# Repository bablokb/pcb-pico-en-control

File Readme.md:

Pico EN Control
===============

This is a simple breakout to control the enable pin of a Pico to
minimize battery usage.

Functions:
  * Enable using a button, a RTC or an external signal
  * Disable by pulling a GPIO high from your program
  * keep time

The target application of this design is a program that runs in
intervals. After startup the program executes it's tasks, sets
the next wakup time and then pulls the "done"-GPIO high.
The circuitry then pulls the enable-pin low, thus limiting the
battery consumption to a very low level.

The design of the breakout allows it to be connected directly on the bottom
side of the pico. Note that the breakout uses a solderless layout for the
pins, i.e. it will hold by friction. But don't expect miracles, it may
or may not work depending on your pins. For production use, you should
definitely solder the breakout.

Hardware Components
-------------------

A D-type flip-flop drives the enable pin of the Pico. A
button, the RTC or an external signal will reset the flip-flop,
which pulls the enable pin high.

The "done"-pin of the Pico is connected to the CLK-pin of
the flip-flop. A rising edge will toggle the enable pin.

PCB
---

PCB design files are in `pico-en-control.kicad`.

Ready to use production files for JLCPCB are in `production_files`.

Software
--------

A simple example program implemented in CircuitPython
is provided in `src/main.py`. The software provides some boilerplate
code for timer and alarm-based wake up.

In timer-mode, the program uses the countdown-timer of the rtc. It
blinks the on-board LED for ten seconds, then goes to sleep for 15 seconds.

Measured current:

For longer intervals alarm-based wake up is more suitable. Since the rtc
does not support seconds for alarms, it will always fire on "full minutes".
The current measurement demonstrates this behavior (the first off-interval
is shorter than the following off-intervals):

Current in off-state is about 75µA (with CLKOUT disabled):

License
-------

[![CC BY-SA 4.0][cc-by-sa-shield]][cc-by-sa]

This work is licensed under a
[Creative Commons Attribution-ShareAlike 4.0 International
License][cc-by-sa].

[![CC BY-SA 4.0][cc-by-sa-image]][cc-by-sa]

[cc-by-sa]: http://creativecommons.org/licenses/by-sa/4.0/
[cc-by-sa-image]: https://licensebuttons.net/l/by-sa/4.0/88x31.png
[cc-by-sa-shield]:
https://img.shields.io/badge/License-CC%20BY--SA%204.0-lightgrey.svg

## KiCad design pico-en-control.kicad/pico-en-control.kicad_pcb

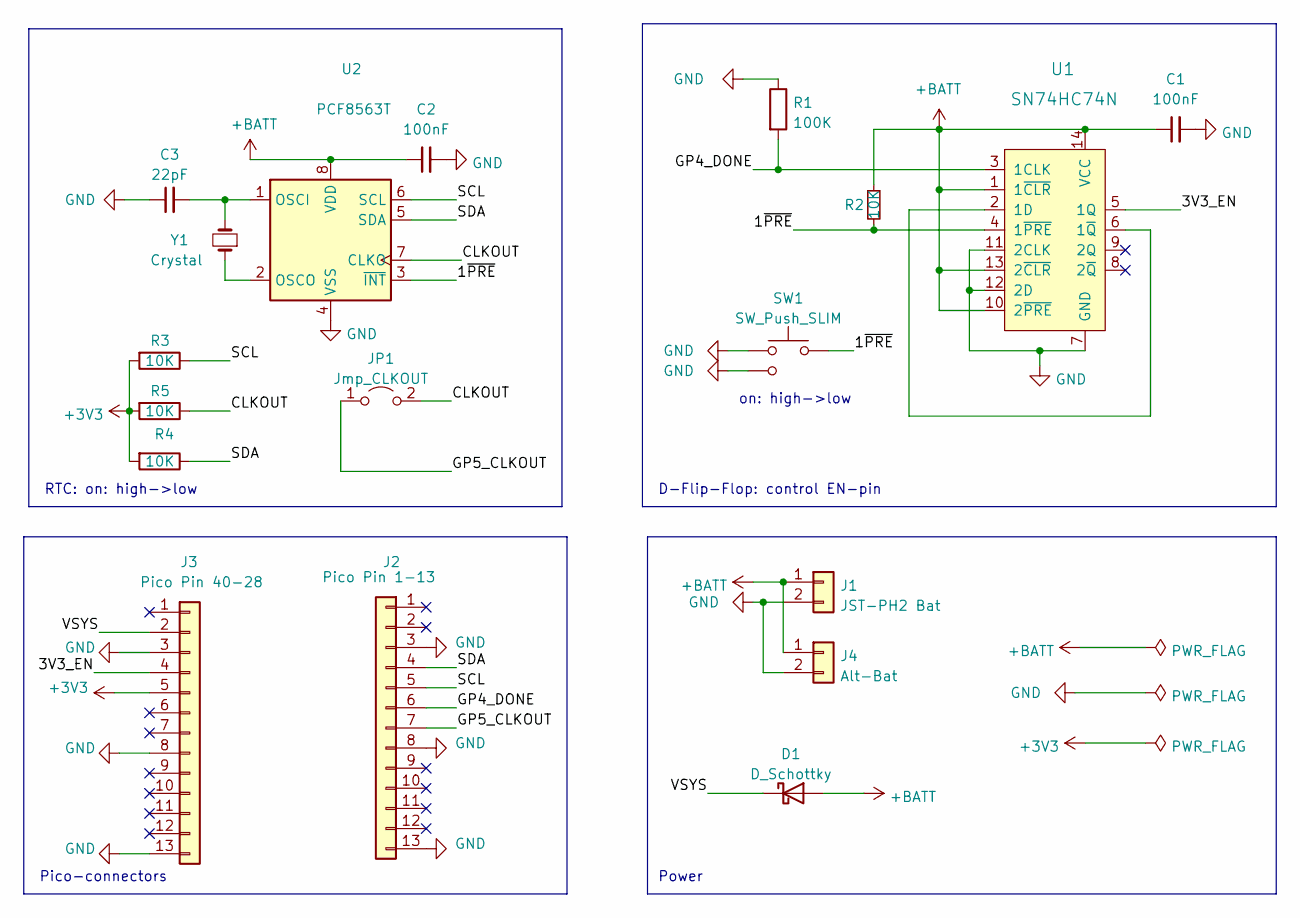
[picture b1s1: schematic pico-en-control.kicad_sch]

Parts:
C1, C2: 100nF; C_0402_1005Metric; LCSC C1525
C3: 22pF; C_0402_1005Metric; LCSC C1555
D1: D_Schottky; D_SMA; LCSC C2480
J1: JST-PH2 Bat; JST_PH_S2B-PH-SM4-TB_1x02-1MP_P2.00mm_Horizontal
J2: Pico Pin 1-13; Connector_1x13_no_solder
J3: Pico Pin 40-28; Connector_1x13_no_solder
J4: Alt-Bat; PinHeader_1x02_P2.54mm_Vertical
JP1: Jmp_CLKOUT; SolderJumper-2_P1.3mm_Open_Pad1.0x1.5mm
R1: 100K; R_0402_1005Metric; LCSC C25741
R2, R3, R4, R5: 10K; R_0402_1005Metric; LCSC C25744
SW1: SW_Push_SLIM; SW_PUSH_SLIM_1x4
U1: SN74HC74N; SOIC-14_3.9x8.7mm_P1.27mm; MPN SN74HC74N; Digi-Key_PN 296-1602-5-ND
U2: PCF8563T; SOIC-8_3.9x4.9mm_P1.27mm; LCSC C7440
Y1: Crystal; Crystal_SMD_3215-2Pin_3.2x1.5mm; LCSC C32346

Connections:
+3V3: J3.5, R3.2, R4.2, R5.2
+BATT: C1.1, C2.1, D1.2 (A), J1.1, J4.1, R2.1, U1.1 (1~CLR), U1.10 (2~PRE), U1.13 (2~CLR), U1.14 (VCC), U2.8 (VDD)
/1~PRE: R2.2, SW1.2, U1.4 (1~PRE), U2.3 (~INT)
/3V3_EN: J3.4, U1.5 (1Q)
/CLKOUT: JP1.2 (B), R5.1, U2.7 (CLKO)
/GP4_DONE: J2.6, R1.2, U1.3 (1CLK)
/GP5_CLKOUT: J2.7, JP1.1 (A)
/SCL: J2.5, R3.1, U2.6 (SCL)
/SDA: J2.4, R4.1, U2.5 (SDA)
/VSYS: D1.1 (K), J3.2
GND: C1.2, C2.2, C3.1, J1.2, J2.3, J2.8, J2.13, J3.3, J3.8, J3.13, J4.2, R1.1, SW1.1, SW1.3 (1), U1.7 (GND), U1.11 (2CLK), U1.12 (2D), U2.4 (VSS)
unnamed: C3.2, U2.1 (OSCI), Y1.2
unnamed: U1.2 (1D), U1.6 (1~Q)
unnamed: U2.2 (OSCO), Y1.1

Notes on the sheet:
Power
D-Flip-Flop: control EN-pin
Pico-connectors
RTC: on: high->low
on: high->low

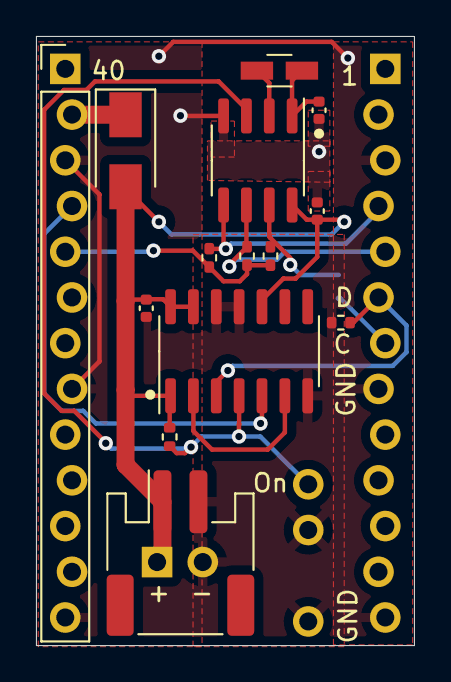
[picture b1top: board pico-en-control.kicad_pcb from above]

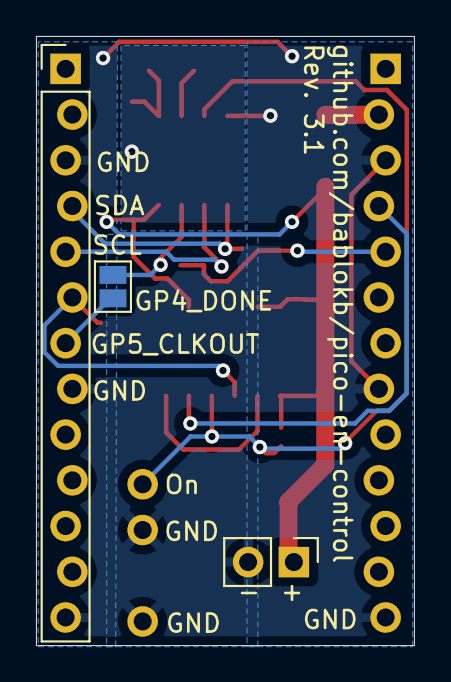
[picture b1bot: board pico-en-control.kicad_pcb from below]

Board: 2 copper layers, 21.0 x 33.8 mm, 18 parts (3 on the bottom side), 14 nets.

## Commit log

2023-01-25 fixed path of xml
2023-02-02 draft routing
2023-02-03 switched to 13-pin connectors
2023-02-03 DRC ok
2023-02-09 Rev2
2023-02-17 Rev3
2023-02-17 Rev 3.1 (prod)
2023-03-02 added non-versioned files for example
2023-03-02 updated with details about the PCB and the sample program
2023-03-06 code cleanup
2023-03-06 renamed file current.png -> current-timer.png
2023-03-06 support alarm-based wake up
2023-03-06 resized and rotated images
2023-03-15 minor changes
2023-05-12 migrated to new version of adafruit_pcf8563
2023-05-12 added link to power-off graphics
2023-05-12 disable clkout to save some 2µA
2023-05-12 update for new measurement with 75µA current in off-state
